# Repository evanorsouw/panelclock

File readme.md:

# 1 Introduction

This project was the result of wanting to do something with those 64x64 RGB panels you see so often. 
The HUB75 interface that they use requires constant updating at a speed of (max) 30MHz.
I saw very clever solutions using Arduino and ESP boards but they lacked the ability to refresh
at a high enough frequency or at 8 bit color depth. I have always wanted to do something with an FPGA
and this is my first projects integrating the ICE40HX4K FPGA chip into a design.

Since I like clocks (as so many people) in all their shapes I decided create a clock from it.

> _This repository contains all files for the hardware (Kicad), FPGA (VHDL via IceCUBE2), software (C++/FreeRTOS/PlatformIO) and the mechanical stl files (design was made from Fusion360 but these are not in this archive).  
However much more documentation is needed not only for others, but also for myself as a reference later on._

It clock comes in 2 flavors, as a double panel in 128x64 landscape or portrait mode and as a single 64x64 panel.

# 1.1 History

The initial idea began somewhere 2019 with the purchase of a MAX1000 FPGA board. For this I created a small breakout board to 2 HUB75 connectors. The FPGA was used to do 25Hz rendering at 8bit color depth. The USB connector on the [MAX1000 board](https://duckduckgo.com/?t=ffab&q=google+max1000+trenz&ia=web) was used to push screen updates from the Linux system to the FPGA. The software was C# that I developed and tested on Windows in a simulation and run on Linux afterwards. This setup worked ok but required an external PC (NUC) running linux. You can still find this code in the `old` directory.

I wanted a compact stand-alone setup so in 2024 I started on designing a standalone system. Since at that time the bare MAX10 chip was not easily for sale for searching for an alternative I ran into the ICE40 FPGA. Less capable but more than enough for my purpose. Only real drawback was that internal FPGA memory was far less resulting in the need to add some external static RAM. 

Software wise there was a lot of trial-and-erroring and a lot of hurdles to get over. At the end it all worked nicely but it lacked unittests and the code is quite messy at places. Specifically getting the graphics rendering up to speed was challenging. Running bare metal, the very simple task of drawing 
antialised graphics took months to complete. The solution here was to have the ability to draw an antialised triangle and use that as basis for the rest. Text drawing was done using the brilliant [libschrift](https://github.com/tomolt/libschrift) library that allows me to render TTF fonts.

So in the end, now I know what I want and need I should rewrite much of the software and structurally add unittest...

# 2 Hardware

The hardware used in this project is relatively simple, with an ESP32 as main controller running the clock software and continuously pushing newly rendered images to the FPGA.
An ICE40 FPGA is used to refresh the images on 2 HUB75 connected displays.
Other than these 2 main components, the is a static 256KB RAM chip where the FPGA stores the received images (24KB each) for displaying, a simple USB based powersupply for 3v3 and 1v8, the well known CH340 chip for programming and downloading. There is also a MAX983657 amplifier on there but software wise it is not used yet. Most parts of this schematic are from standard application notes.

 The assembled 2-layer PCB looks like this; 

# 3 Software

The software for the FPGA is VHDL compiled with the free (for personal use) [ICECube2 software](https://www.latticesemi.com/iCEcube2) from Lattice. 

The software for the ESP32 is developed using VisualCode and PlatformIO using FreeRTOS. The FPGA is configured via the ESP32 at startup via SPI. The ESP32 is setup to use A/B bootmode. When the software runs it will periodically (daily, weekly, monthly) check a configurable website if new software is available. If new software is found, it is installed and run. A special button combo during boot will revert the system back it fails.

The application uses 2 bitmaps that I toggle between. While 1 bitmap is being rendered, the other is sent to the FPGA. Since the ESP32 has 2 cores I typially use 1 core for rendering and the other for transferring the data. Some additional tasks run periodically like syncing with NTP and retrieving weather info.

The system has 3 buttons, `up`,`down` and `select` that are used for configuring the system. There are a number of configurable items for Wifi, NTP server, timezone etc. For weather information, [openweather](https://openweathermap.org/api) is used which requires you to request a free API key. This key also needs to be entered here together with your location. GUI-wise there is not much to configure the display is fixed but does display a variety of periodic animations, 5-minutes tick animations, expanding circles, game of life. 

A [usermanual](doc/usermanual.md) is found here.

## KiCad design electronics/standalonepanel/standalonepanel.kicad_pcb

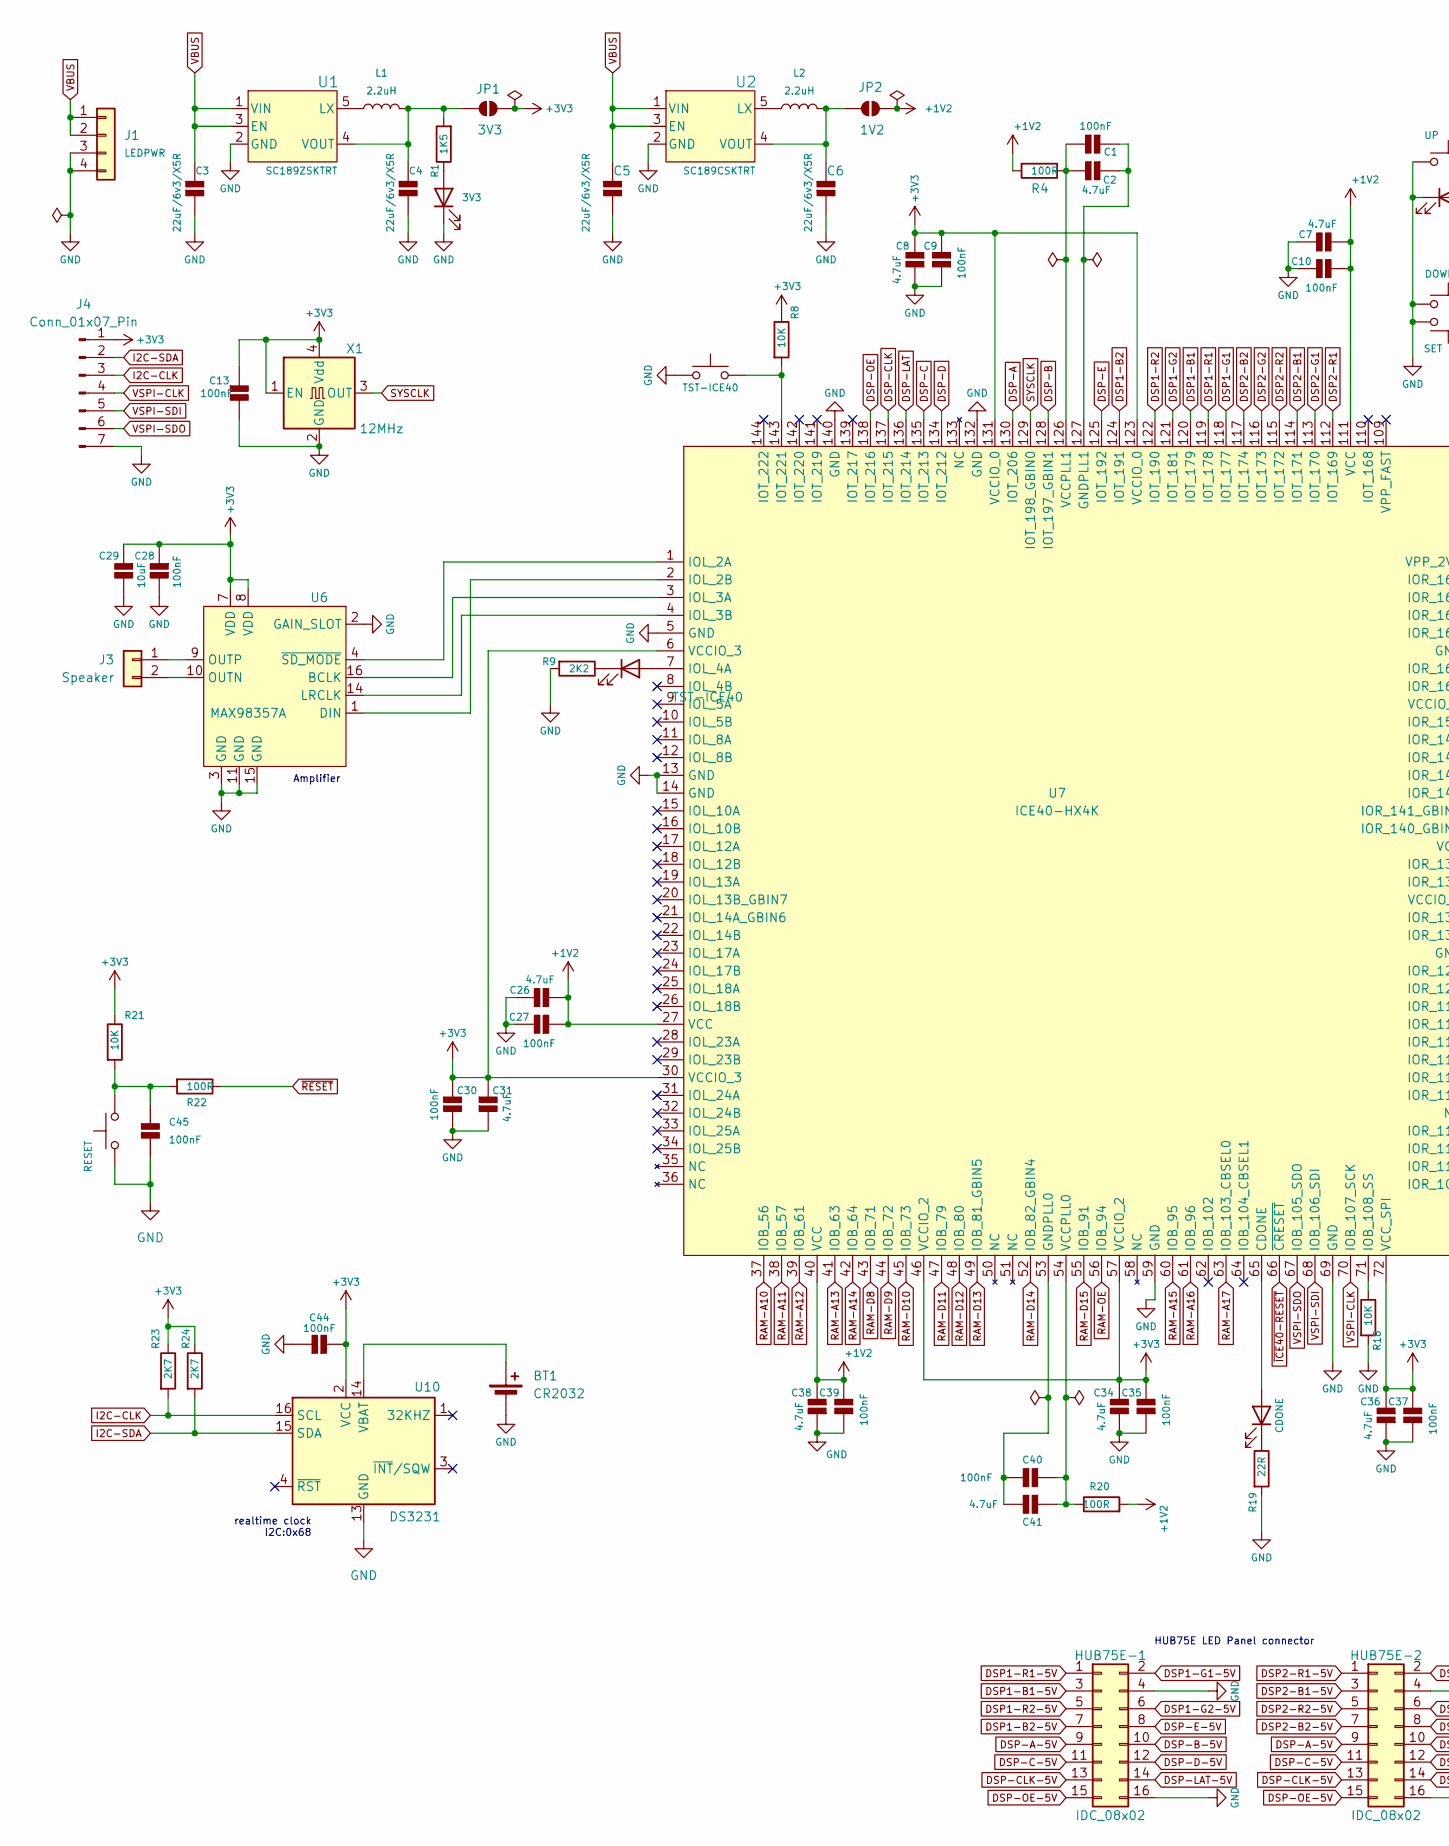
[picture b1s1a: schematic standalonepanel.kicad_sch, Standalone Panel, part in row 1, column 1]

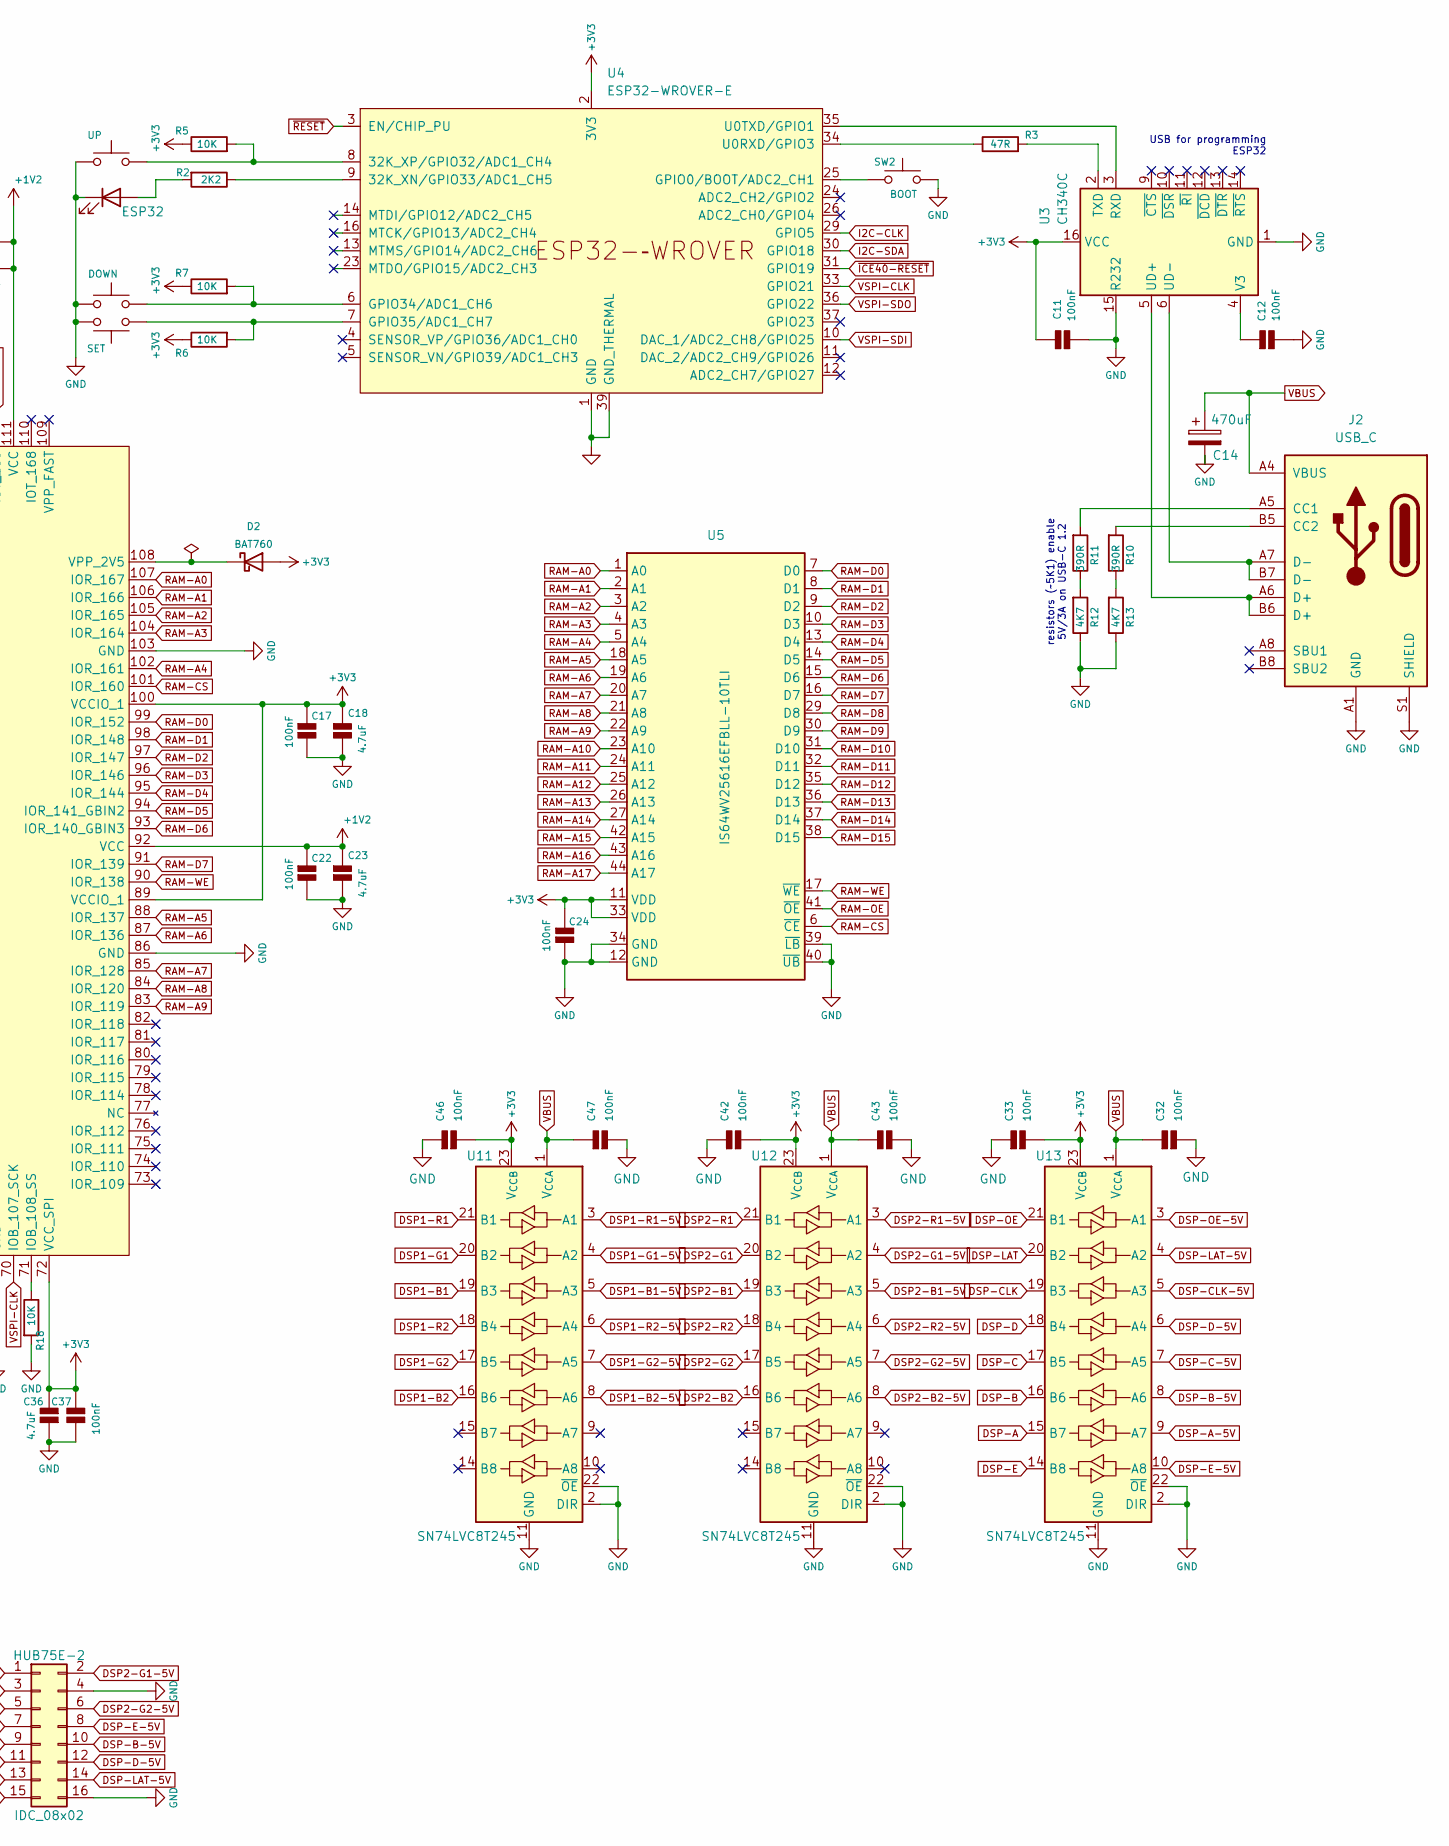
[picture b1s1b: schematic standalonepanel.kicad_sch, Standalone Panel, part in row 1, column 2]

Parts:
BT1: CR2032; cr2032_smd_clip
C1, C9, C10, C11, C12, C13, C17, C22, C24, C27, C28, C30, C32, C33, C35, C37, C39, C40, C42, C43, C44, C45, C46, C47: 100nF; C_0805_2012Metric_Pad1.18x1.45mm_HandSolder
C2, C7, C8, C18, C23, C26, C31, C34, C36, C38, C41: 4.7uF; C_0805_2012Metric_Pad1.18x1.45mm_HandSolder
C3, C4, C5, C6: 22uF/6v3/X5R; C_0805_2012Metric_Pad1.18x1.45mm_HandSolder
C14: 470uF; C_Elec_8x10.2
C29: 10uF; C_0805_2012Metric_Pad1.18x1.45mm_HandSolder
D2: BAT760; D_SOD-323
HUB75E-1, HUB75E-2: IDC_08x02; IDC-Header_2x08_P2.54mm_Horizontal
J1: LEDPWR; JST_VH_1x04_P3.96mm_Horizontal
J2: USB_C; USB_C_Receptacle _12pins
J3: Speaker; JST_XH_S2B-XH-A_1x02_P2.50mm_Horizontal
J4: Conn_01x07_Pin; PinHeader_1x07_P2.54mm_Vertical
JP1: 3V3; SolderJumper-2_P1.3mm_Open_RoundedPad1.0x1.5mm
JP2: 1V2; SolderJumper-2_P1.3mm_Open_RoundedPad1.0x1.5mm
L1, L2: 2.2uH; Inductor-040420
LED1: 3V3; LED_1206_3216Metric_Pad1.42x1.75mm_HandSolder
LED2: ESP32; LED_1206_3216Metric_Pad1.42x1.75mm_HandSolder
LED3: TST-ICE40; LED_1206_3216Metric_Pad1.42x1.75mm_HandSolder
LED5: CDONE; LED_1206_3216Metric_Pad1.42x1.75mm_HandSolder
R1: 1K5; R_1206_3216Metric_Pad1.30x1.75mm_HandSolder
R2, R9: 2K2; R_1206_3216Metric_Pad1.30x1.75mm_HandSolder
R3: 47R; R_1206_3216Metric_Pad1.30x1.75mm_HandSolder
R4, R20, R22: 100R; R_1206_3216Metric_Pad1.30x1.75mm_HandSolder
R5, R6, R7, R8, R18, R21: 10K; R_1206_3216Metric_Pad1.30x1.75mm_HandSolder
R10, R11: 390R; R_1206_3216Metric_Pad1.30x1.75mm_HandSolder
R12, R13: 4K7; R_1206_3216Metric_Pad1.30x1.75mm_HandSolder
R19: 22R; R_1206_3216Metric_Pad1.30x1.75mm_HandSolder
R23, R24: 2K7; R_1206_3216Metric_Pad1.30x1.75mm_HandSolder
SW1: UP; SW_Tactile_SKHH_Angled
SW2: BOOT; SW_SPST_FSMSM
SW3: SET; SW_Tactile_SKHH_Angled
SW4: DOWN; SW_Tactile_SKHH_Angled
SW5: TST-ICE40; SW_SPST_FSMSM
SW6: RESET; SW_SPST_FSMSM
U1: SC189ZSKTRT; SOT23-5-SC189_SEM
U2: SC189CSKTRT; SOT23-5-SC189_SEM
U3: CH340C; SOIC-16_3.9x9.9mm_P1.27mm
U4: ESP32-WROVER-E
U5: IS64WV25616EFBLL-10TLI; TSOP-II-44_10.16x18.41mm_P0.8mm
U6: MAX98357A; TQFN-16-1EP_3x3mm_P0.5mm_EP1.6x1.6mm
U7: ICE40-HX4K; TQFP-144_20x20mm_P0.5mm
U10: DS3231; SOIC-16W_7.5x10.3mm_P1.27mm
U11, U12, U13: SN74LVC8T245; TSSOP-24_4.4x7.8mm_P0.65mm
X1: 12MHz; Oscillator_SMD_EuroQuartz_XO91-4Pin_7.0x5.0mm_HandSoldering

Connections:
+1V2: C7.2, C10.2, C22.1, C23.1, C26.2, C27.2, C38.2, C39.2, JP2.2 (B), R4.2, R20.2, U7.27 (VCC), U7.40 (VCC), U7.92 (VCC), U7.111 (VCC)
+3V3: C8.2, C9.2, C11.1, C13.1, C17.1, C18.1, C24.1, C28.1, C29.1, C30.1, C31.1, C33.2, C34.2, C35.2, C36.2, C37.2, C42.2, C44.2, C46.2, D2.2 (A), J4.1, JP1.2 (B), R5.1, R6.1, R7.1, R8.1, R21.1, R23.1, R24.1, U3.16 (VCC), U4.2 (3V3), U5.11 (VDD), U5.33 (VDD), U6.7 (VDD), U6.8 (VDD), U7.6 (VCCIO_3), U7.30 (VCCIO_3), U7.46 (VCCIO_2), U7.57 (VCCIO_2), U7.72 (VCC_SPI), U7.89 (VCCIO_1), U7.100 (VCCIO_1), U7.123 (VCCIO_0), U7.131 (VCCIO_0), U10.2 (VCC), U11.23 (V_{CCB}), U11.24 (V_{CCB}), U12.23 (V_{CCB}), U12.24 (V_{CCB}), U13.23 (V_{CCB}), U13.24 (V_{CCB}), X1.1 (EN), X1.4 (Vdd)
DSP1-B1: U7.120 (IOT_179), U11.19 (B3)
DSP1-B1-5V: HUB75E-1.3, U11.5 (A3)
DSP1-B2: U7.124 (IOT_191), U11.16 (B6)
DSP1-B2-5V: HUB75E-1.7, U11.8 (A6)
DSP1-G1: U7.118 (IOT_177), U11.20 (B2)
DSP1-G1-5V: HUB75E-1.2, U11.4 (A2)
DSP1-G2: U7.121 (IOT_181), U11.17 (B5)
DSP1-G2-5V: HUB75E-1.6, U11.7 (A5)
DSP1-R1: U7.119 (IOT_178), U11.21 (B1)
DSP1-R1-5V: HUB75E-1.1, U11.3 (A1)
DSP1-R2: U7.122 (IOT_190), U11.18 (B4)
DSP1-R2-5V: HUB75E-1.5, U11.6 (A4)
DSP2-B1: U7.114 (IOT_171), U12.19 (B3)
DSP2-B1-5V: HUB75E-2.3, U12.5 (A3)
DSP2-B2: U7.117 (IOT_174), U12.16 (B6)
DSP2-B2-5V: HUB75E-2.7, U12.8 (A6)
DSP2-G1: U7.113 (IOT_170), U12.20 (B2)
DSP2-G1-5V: HUB75E-2.2, U12.4 (A2)
DSP2-G2: U7.116 (IOT_173), U12.17 (B5)
DSP2-G2-5V: HUB75E-2.6, U12.7 (A5)
DSP2-R1: U7.112 (IOT_169), U12.21 (B1)
DSP2-R1-5V: HUB75E-2.1, U12.3 (A1)
DSP2-R2: U7.115 (IOT_172), U12.18 (B4)
DSP2-R2-5V: HUB75E-2.5, U12.6 (A4)
DSP-A: U7.130 (IOT_206), U13.15 (B7)
DSP-A-5V: HUB75E-1.9, HUB75E-2.9, U13.9 (A7)
DSP-B: U7.128 (IOT_197_GBIN1), U13.16 (B6)
DSP-B-5V: HUB75E-1.10, HUB75E-2.10, U13.8 (A6)
DSP-C: U7.135 (IOT_213), U13.17 (B5)
DSP-C-5V: HUB75E-1.11, HUB75E-2.11, U13.7 (A5)
DSP-CLK: U7.137 (IOT_215), U13.19 (B3)
DSP-CLK-5V: HUB75E-1.13, HUB75E-2.13, U13.5 (A3)
DSP-D: U7.134 (IOT_212), U13.18 (B4)
DSP-D-5V: HUB75E-1.12, HUB75E-2.12, U13.6 (A4)
DSP-E: U7.125 (IOT_192), U13.14 (B8)
DSP-E-5V: HUB75E-1.8, HUB75E-2.8, U13.10 (A8)
DSP-LAT: U7.136 (IOT_214), U13.20 (B2)
DSP-LAT-5V: HUB75E-1.14, HUB75E-2.14, U13.4 (A2)
DSP-OE: U7.138 (IOT_216), U13.21 (B1)
DSP-OE-5V: HUB75E-1.15, HUB75E-2.15, U13.3 (A1)
GND: BT1.2 (-), C3.2, C4.2, C5.2, C6.2, C7.1, C8.1, C9.1, C10.1, C11.2, C12.2, C13.2, C14.2, C17.2, C18.2, C22.2, C23.2, C24.2, C26.1, C27.1, C28.2, C29.2, C30.2, C31.2, C32.2, C33.1, C34.1, C35.1, C36.1, C37.1, C38.1, C39.1, C42.1, C43.2, C44.1, C45.2, C46.1, C47.2, HUB75E-1.4, HUB75E-1.16, HUB75E-2.4, HUB75E-2.16, J1.3, J1.4, J2.A1 (GND), J2.A12 (GND), J2.B1 (GND), J2.B12 (GND), J2.S1 (SHIELD), J4.7, LED1.1 (K), LED2.1 (K), R9.2, R12.1, R13.1, R18.2, R19.2, SW1.1, SW2.2, SW3.1, SW4.1, SW5.1, SW6.1, U1.2 (GND), U2.2 (GND), U3.1 (GND), U3.15 (R232), U4.1 (GND), U4.15 (GND), U4.38 (GND), U4.39 (GND_THERMAL), U5.12 (GND), U5.34 (GND), U5.39 (~LB), U5.40 (~UB), U6.2 (GAIN_SLOT), U6.3 (GND), U6.11 (GND), U6.15 (GND), U7.5 (GND), U7.13 (GND), U7.14 (GND), U7.59 (GND), U7.69 (GND), U7.86 (GND), U7.103 (GND), U7.132 (GND), U7.140 (GND), U10.5 (GND), U10.6 (GND), U10.7 (GND), U10.8 (GND), U10.9 (GND), U10.10 (GND), U10.11 (GND), U10.12 (GND), U10.13 (GND), U11.2 (DIR), U11.11 (GND), U11.12 (GND), U11.13 (GND), U11.22 (~OE), U12.2 (DIR), U12.11 (GND), U12.12 (GND), U12.13 (GND), U12.22 (~OE), U13.2 (DIR), U13.11 (GND), U13.12 (GND), U13.13 (GND), U13.22 (~OE), X1.2 (GND)
I2C-CLK: J4.3, R23.2, U4.29 (GPIO5), U10.16 (SCL)
I2C-SDA: J4.2, R24.2, U4.30 (GPIO18), U10.15 (SDA)
unnamed: BT1.1 (+), U10.14 (VBAT)
unnamed: C45.1, R21.2, R22.2, SW6.2
unnamed: D2.1 (K), U7.108 (VPP_2V5)
unnamed: J2.A5 (CC1), R11.2
unnamed: J2.B5 (CC2), R10.2
unnamed: J3.1, U6.9 (OUTP)
unnamed: J3.2, U6.10 (OUTN)
unnamed: C4.1, JP1.1 (A), L1.2, R1.2, U1.4 (VOUT)
unnamed: C6.1, JP2.1 (A), L2.2, U2.4 (VOUT)
unnamed: LED1.2 (A), R1.1
unnamed: LED2.2 (A), R2.2
unnamed: LED3.2 (A), U7.7 (IOL_4A)
unnamed: LED3.1 (K), R9.1
unnamed: LED5.2 (A), U7.65 (CDONE)
unnamed: LED5.1 (K), R19.1
unnamed: R10.1, R13.2
unnamed: R11.1, R12.2
unnamed: L1.1, U1.5 (LX)
unnamed: L2.1, U2.5 (LX)
unnamed: U3.3 (RXD), U4.35 (U0TXD/GPIO1)
unnamed: R3.2, U3.2 (TXD)
unnamed: J2.A6 (D+), J2.B6 (D+), U3.5 (UD+)
unnamed: J2.A7 (D-), J2.B7 (D-), U3.6 (UD-)
unnamed: C12.1, U3.4 (V3)
unnamed: R2.1, U4.9 (32K_XN/GPIO33/ADC1_CH5)
unnamed: R5.2, SW1.2, U4.8 (32K_XP/GPIO32/ADC1_CH4)
unnamed: SW2.1, U4.25 (GPIO0/BOOT/ADC2_CH1)
unnamed: R7.2, SW4.2, U4.6 (GPIO34/ADC1_CH6)
unnamed: R6.2, SW3.2, U4.7 (GPIO35/ADC1_CH7)
unnamed: R3.1, U4.34 (U0RXD/GPIO3)
unnamed: U6.16 (BCLK), U7.3 (IOL_3A)
unnamed: U6.1 (DIN), U7.2 (IOL_2B)
unnamed: U6.14 (LRCLK), U7.4 (IOL_3B)
unnamed: U6.4 (~SD_MODE), U7.1 (IOL_2A)
unnamed: C40.2, C41.2, U7.53 (GNDPLL0)
unnamed: C1.1, C2.1, U7.127 (GNDPLL1)
unnamed: R18.1, U7.71 (IOB_108_SS)
unnamed: R8.2, SW5.2, U7.143 (IOT_221)
unnamed: C40.1, C41.1, R20.1, U7.54 (VCCPLL0)
unnamed: C1.2, C2.2, R4.1, U7.126 (VCCPLL1)
RAM-A0: U5.1 (A0), U7.107 (IOR_167)
RAM-A1: U5.2 (A1), U7.106 (IOR_166)
RAM-A2: U5.3 (A2), U7.105 (IOR_165)
RAM-A3: U5.4 (A3), U7.104 (IOR_164)
RAM-A4: U5.5 (A4), U7.102 (IOR_161)
RAM-A5: U5.18 (A5), U7.88 (IOR_137)
RAM-A6: U5.19 (A6), U7.87 (IOR_136)
RAM-A7: U5.20 (A7), U7.85 (IOR_128)
RAM-A8: U5.21 (A8), U7.84 (IOR_120)
RAM-A9: U5.22 (A9), U7.83 (IOR_119)
RAM-A10: U5.23 (A10), U7.37 (IOB_56)
RAM-A11: U5.24 (A11), U7.38 (IOB_57)
RAM-A12: U5.25 (A12), U7.39 (IOB_61)
RAM-A13: U5.26 (A13), U7.41 (IOB_63)
RAM-A14: U5.27 (A14), U7.42 (IOB_64)
RAM-A15: U5.42 (A15), U7.60 (IOB_95)
RAM-A16: U5.43 (A16), U7.61 (IOB_96)
RAM-A17: U5.44 (A17), U7.63 (IOB_103_CBSEL0)
RAM-CS: U5.6 (~CE), U7.101 (IOR_160)
RAM-D0: U5.7 (D0), U7.99 (IOR_152)
RAM-D1: U5.8 (D1), U7.98 (IOR_148)
RAM-D2: U5.9 (D2), U7.97 (IOR_147)
RAM-D3: U5.10 (D3), U7.96 (IOR_146)
RAM-D4: U5.13 (D4), U7.95 (IOR_144)
RAM-D5: U5.14 (D5), U7.94 (IOR_141_GBIN2)
RAM-D6: U5.15 (D6), U7.93 (IOR_140_GBIN3)
RAM-D7: U5.16 (D7), U7.91 (IOR_139)
RAM-D8: U5.29 (D8), U7.43 (IOB_71)
RAM-D9: U5.30 (D9), U7.44 (IOB_72)
RAM-D10: U5.31 (D10), U7.45 (IOB_73)
RAM-D11: U5.32 (D11), U7.47 (IOB_79)
RAM-D12: U5.35 (D12), U7.48 (IOB_80)
RAM-D13: U5.36 (D13), U7.49 (IOB_81_GBIN5)
RAM-D14: U5.37 (D14), U7.52 (IOB_82_GBIN4)
RAM-D15: U5.38 (D15), U7.55 (IOB_91)
RAM-OE: U5.41 (~OE), U7.56 (IOB_94)
RAM-WE: U5.17 (~WE), U7.90 (IOR_138)
SYSCLK: U7.129 (IOT_198_GBIN0), X1.3 (OUT)
VBUS: C3.1, C5.1, C14.1, C32.1, C43.1, C47.1, J1.1, J1.2, J2.A4 (VBUS), J2.A9 (VBUS), J2.B4 (VBUS), J2.B9 (VBUS), U1.1 (VIN), U1.3 (EN), U2.1 (VIN), U2.3 (EN), U11.1 (V_{CCA}), U12.1 (V_{CCA}), U13.1 (V_{CCA})
VSPI-CLK: J4.4, U4.33 (GPIO21), U7.70 (IOB_107_SCK)
VSPI-SDI: J4.5, U4.10 (DAC_1/ADC2_CH8/GPIO25), U7.68 (IOB_106_SDI)
VSPI-SDO: J4.6, U4.36 (GPIO22), U7.67 (IOB_105_SDO)
~ICE40-RESET: U4.31 (GPIO19), U7.66 (~CRESET)
~RESET: R22.1, U4.3 (EN/CHIP_PU)

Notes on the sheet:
Amplifier
resistors (~5K1) enable 5V/3A on USB-C 1.2
USB for programming ESP32
HUB75E LED Panel connector
realtime clock I2C:0x68

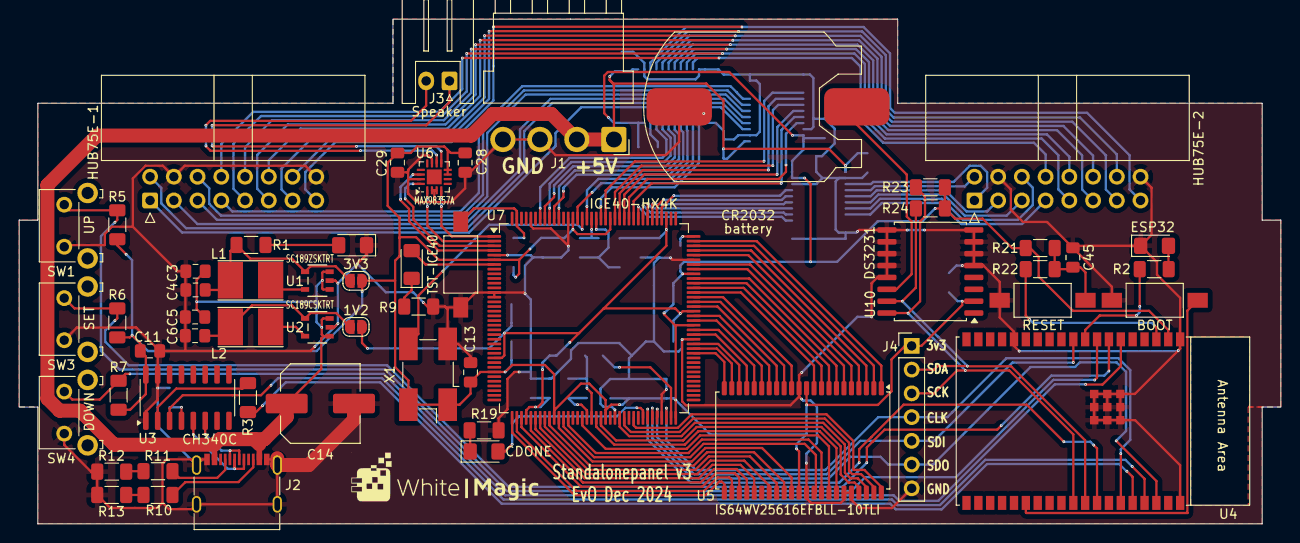
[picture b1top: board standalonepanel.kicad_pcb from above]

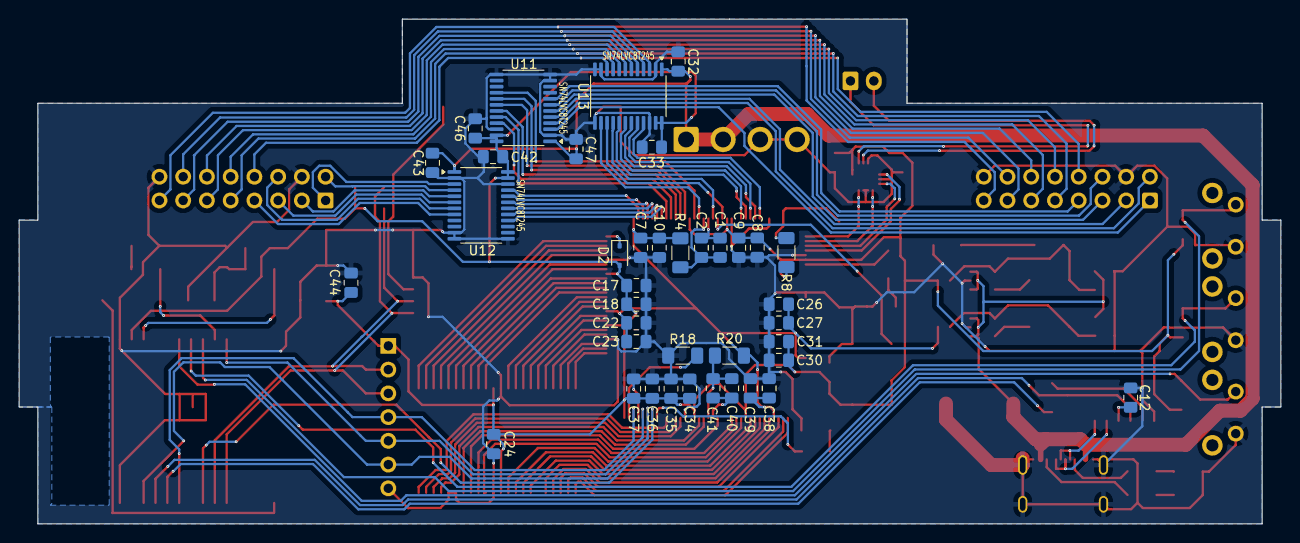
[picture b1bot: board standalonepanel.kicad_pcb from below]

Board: 2 copper layers, 135.0 x 54.0 mm, 95 parts (39 on the bottom side), 129 nets.

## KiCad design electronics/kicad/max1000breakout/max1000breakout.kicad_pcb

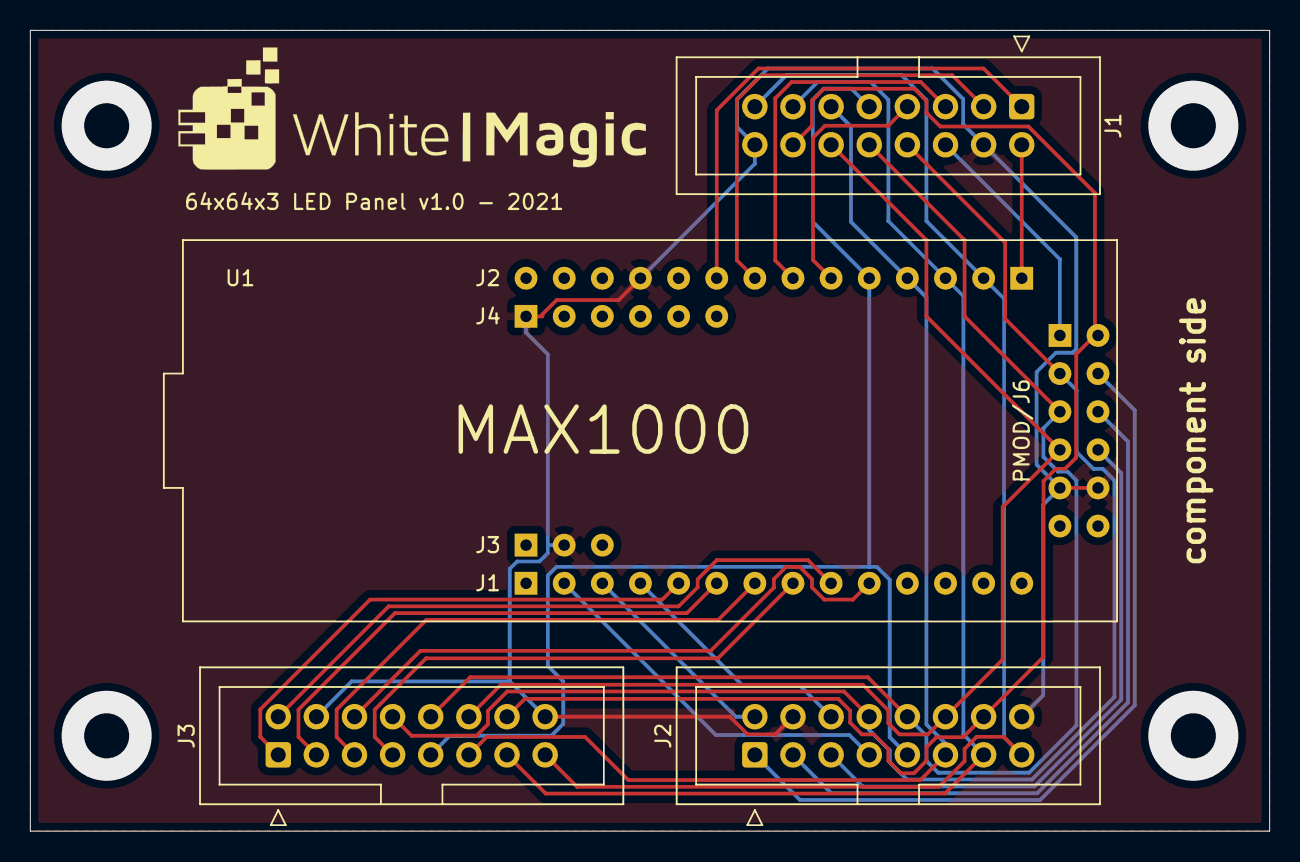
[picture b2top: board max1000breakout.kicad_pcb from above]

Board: 2 copper layers, 82.6 x 53.3 mm, 5 parts (0 on the bottom side), 27 nets.

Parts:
J1, J2, J3: Conn_02x08_Odd_Even; IDC-Header_2x08_P2.54mm_Vertical
Ref**: Val**; whitemagic_logo
U1: MAX1000

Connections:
/gnd: J1.4, J1.16, J2.4, J2.16, J3.4, J3.16, U1.4, U1.33, U1.39, U1.42, U1.44
/m6: J1.1, U1.6
/m7: J1.3, U1.7
/m8: J1.5, U1.8
/m9: J1.7, U1.9
/m10: J1.9, J2.9, J3.9, U1.10
/m11: J1.11, J2.11, J3.11, U1.11
/m12: J1.13, J2.13, J3.13, U1.12
/m13: J1.15, J2.15, J3.15, U1.13
/m14: J1.2, U1.14
/m15: J1.6, U1.29
/m16: J1.8, J2.8, J3.8, U1.30
/m17: J1.10, J2.10, J3.10, U1.31
/m18: J1.12, J2.12, J3.12, U1.32
/m19: J1.14, J2.14, J3.14, U1.35
/m20: J2.1, U1.36
/m21: J2.3, U1.37
/m22: J2.5, U1.38
/m23: J2.7, U1.16
/m24: J2.2, U1.17
/m25: J2.6, U1.18
/m26: J3.1, U1.19
/m27: J3.3, U1.20
/m28: J3.5, U1.21
/m29: J3.7, U1.22
/m30: J3.2, U1.23
/m31: J3.6, U1.24

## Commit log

2021-03-24 initial checkin
2021-03-27 first working 2x64x64 panel 3 bit colors
2021-03-27 single color white edge
2021-03-27 working true color 8bit depth, successive layers
2021-04-21 working 64x64 7 bit depth solution (max bit-depth with rock stable display)
2021-04-21 extracted rgb values from 6124 to overarching controller
2021-04-21 added logarithmic table
2021-05-18 working truecolor version with USB interface
2021-05-23 added linear RGB memory added log intensity correction
2021-05-23 updated files to ignore
2021-05-23 removed obsolete files
2021-05-23 increased comm speed to 3.75MBaud
2021-05-24 added brightness control
2021-05-24 prepared for 2 panels
2021-05-31 added segment clock and initial textpanel
2021-06-01 update of textpanel
2021-06-04 fix scale bug
2021-06-04 comm not opened
2021-06-04 various generalizations and tweaks
2021-06-04 initial version of image viewer
2021-06-30 hooked up 2nd display RGB outputs
2021-06-30 added image viewer
2021-07-18 cleanup
2021-07-18 version 1.0
2021-07-25 modified for 64x64x3 breakout board
2021-07-25 removed some unused variables
2021-09-18 added dynamic text label
2021-09-20 added configuration in file
2021-09-21 separated items from scenes
2021-09-21 added crontab added base test project
2021-09-21 start script
2021-09-22 ignored publish directories
2021-09-26 first version with simple expressions
2021-09-26 optimization
2021-09-27 simplified property definitions
2021-09-28 improved expression caabilities
2021-10-02 fixed parsing of true/false literals
2021-10-02 moved to generic visible animation
2021-10-03 first step in scene switching
2021-10-07 refactors
2021-10-09 add conditional expression
2021-10-09 added x3,y3 properties
2021-10-09 unused file
2021-10-09 renamed varlabel to label
2021-10-10 renamed animation to ShowHide refactored logger started Ticker
2021-10-10 ticker hide/show animation
2021-10-13 ticker update
2021-10-24 intermediate update
2021-10-25 major refactor coordinates added environment source
2021-10-31 programmed animated weather icons
2021-11-07 added wind indicator
2022-03-29 added weerlive settings to appsettings fixed error in weather-icon fixed namespaces
2023-04-02 initial commit merging fpga, sw and electronics
2023-04-02 merged sw fpga and pcb repos
2023-04-05 update secondhand, script and drawing of clearnight
2023-09-03 intermediate update fpga files after simulation testing
2023-09-03 external documentation
2023-12-20 various unrelated updates
2023-12-29 got everything working again
2023-12-30 cleaned up changed pinout (pcf) for easier mapping on IDC16 connector
2023-12-31 working version with pixel start address still wrongly interpreted.
2024-01-01 working version with varying addresses
2024-01-01 attempt to add boot logo
2024-01-01 rectangle fill sort-of working
2024-01-04 working version @120MHz
2024-01-05 refactored, but no longer working...
2024-01-06 all working and stable, including ram initialization @120MHz
2024-01-07 added boot image
2024-01-08 extracted commands in separate entities
2024-01-09 fixed reset, fixed height 1 fill bug
2024-01-10 reduced system clock to 30MHz
2024-01-11 extract reset component
2024-01-14 added uart receive with automatic bitrate detection
2024-01-15 tried to fix horizontal offset of 1 pixel - broke it
2024-01-17 cleanup of fpga project
2024-01-17 intermediate checking, changed frequency back to 60MHz...
2024-01-17 updated gitignore
2024-01-21 intermediate checkin - display with c# and flash programmer as intermediate working
2024-01-22 added lut logic - not compiling, too many cells
2024-01-28 working again with new fifo
2024-01-28 working with color lut and fifo of 128 bytes (minimum for 115200 baud)
2024-01-29 all working as planned with 4K of RAM fifo
2024-01-30 geting rid of testsignals
2024-01-31 it appears that all is working now.
2024-02-10 completed LUT and added pixel command
2024-02-12 added display/write to different screens
2024-02-12 a working version with pixel merge in vhdl
2024-02-17 a working antialiased line fixed flickering bug due to write interuption
2024-02-18 preliminary clock working, a slightly too slow on 115200 baud Lut still does not seem to function properly when update via uart
2024-03-20 3D Models v23 all ok, not tested with PCB All electronics designed including PCB - untested
2024-04-16 electronics & PCB v1
2024-05-15 fix schematic errors: - swapped TxD/RxD + resistor CH340 - corrected footprint of DS3231 (was too big) textual errors of U2 (C-variant 1.2V)
2024-05-15 more esp32 datasheets
2024-05-15 Added SPIFFS filesystem with FPGA binary and able to read it from code. remove old ESP32 sourcecode
2024-05-15 initial untested changes for HX4K FPGA
2024-05-23 update vhdl to boot correctly, start of spi interface
2024-06-19 stable working version of update display memory from ESP32
2024-06-23 corrected connections of blue/red removed variables by signals in vhdl that were not used just locally. fixed reset behavior of spi receiver made start with C++ bitmap and ledpanel class
2024-06-30 font rendering using schrift working.
2024-07-02 changed I2C address of MPU6050 from 0x68 to 0x69 to remove conflict with DS3231
2024-07-03 added SDA and SCL pullup resistors swapped teh SDA and SCL lines for DS3231
2024-07-03 working interactions with DS3231 and MPU6050 MPU6050 still unstable readings, maybe hardware (pullup or soldering was too hot)
2024-07-06 got triangles working added rect and demo with seconds dial
2024-07-10 moved old software
2024-08-18 lots of esp32 code changes, started with final application
2024-08-21 added date/time display
2024-08-22 some refactors and weerlive working
2024-08-27 added icon font, many small updates start of boot animation
2024-08-27 wrong sun character
2024-09-10 got bootanimation right
2024-09-10 added all weather image animations
2024-09-11 added clamps for attaching panel to wooden frame (this clamps turned out a little too high though)
2024-09-15 fixed json parse bug and various other improvements
2024-09-26 fixed memory leak
2024-09-27 Schematic v2 PCB version v2 send for production
2024-09-27 moved file
2024-10-03 fixed month-1 bug, removed potential memoryleak
2024-10-19 v2 updates
2024-10-23 fixed rendering of font outside visible area
2024-11-06 added time part of configuration UI, added wifi scanning/connecting.
2024-11-08 fixed some bugs in configuration editor
2024-11-10 added DST flag, addded nvs to store settings, some translations
2024-11-10 fixed some bugs with DST, some configuration refactors
2024-11-10 working version of text editing, needs some more animations (smooth scrolling) and better delete behavior when deleting halfway.
2024-11-14 added scrolling for long config values, fading in between different screens, many refactors in structure,
2024-11-14 added repeat of config selection
2024-11-17 many small fixes, sed SPIRAM to get all working due to out of memory with network calls, this did slow down rendering to 14fps
2024-12-08 removed old max1000 code
2024-12-08 v3 of electronics
2024-12-08 software update for v3
2024-12-10 fixed crash when editing wifi passowrd
2024-12-10 reduced clock from 60MHz to 48MHz to overcome delays introduced in new level shifters
2024-12-10 changes due to new espidf version
2024-12-10 some new SDK changes switch back to 16MB due to other esp module
2024-12-10 fixed fpga bug on first column
2024-12-10 added PCB v3 corner mechanical element
2024-12-12 swapped notion of panel 1 & 2
2024-12-12 added option to flip display (rotate 180) to get USB port on other side. added fading of weather info when not available.
2024-12-12 updated Fusion 3d designs
2024-12-13 fixed weather parsing bug with negative numbers
2024-12-16 add single panel display, refactor graphics/bitmap to support views
2024-12-17 fixed clipping for origin(0,0) views and some bugfixes
2024-12-17 increased main stacksize
2024-12-27 fixed bitmap fonts and compilation program for wmf files
2024-12-27 changes for onepanel application, fixed fonts and numerous bugfixes and improvements
2025-01-03 integrated use of NTP server & timezones setting change callback various bug fixes and improvements full support for the openweather api refactored drawing of weather images
2025-01-03 initdata now clears display attempt to inhibit startup artifacts on display correctly connect fpga led on PCB
2025-01-05 added OTA add version
2025-01-06 many cosmetic changes
2025-01-09 automatic version update many OTA GUI improvements improvement event handling
2025-01-13 removed kicad intermediate directory
2025-01-13 mechanical update
2025-01-13 removed bootscreen and some file cleanup
2025-02-15 added flip option of keys (due to new type2 panel)
2025-02-16 added setup screen (press boot 3sec) to setup different panel layouts.
2025-03-09 many changes, support for vertical panel, added sunrise/set graphics
2025-03-26 added automatic periodic software update checks
2025-04-16 added clock tick animation
2025-07-17 added circleflash animation
2025-07-17 updated mechanics files
2025-08-12 merged improvements from letterclock
2025-08-13 added software update url added software update on predicatable time boundaries
2025-08-13 forgot to add url to gui
2025-10-12 fixed graphics clipping added OTA fastpoll revert after 3H idle cleanup
2025-12-23 added Conways game of life, runs in the background every 7 minutes
2026-02-11 cleanup kicad files and added overview documentation
2026-02-12 added license
